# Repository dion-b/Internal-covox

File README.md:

# Internal-covox
An internal (bracket-mount) Covox Speech Thing-like card, to connect to an internal parallel header.

The Covox Speech Thing is arguably the simplest piece of sound hardware created for the PC, consisting of little more than a resistor ladder DAC and a rudimentary low-pass filter. Because of its relative rarity and extreme simplicity there are already many clone designs. The fact that the patent for the Speech Thing contains a full schematic no doubt helps as well. These clones range from extremely minimal homebrew designs to some commercial sound cards (most notably Aztech Technologies' first generation Soundblaster Pro clones) integrating the functionality.

So, why a new clone? A defining feature of the Speech Thing, and of all common clones not integrated into a sound card/chip is that they are an external design, interfacing with the parallel port of the PC. This means it can be installed without opening the PC case, and can be used on systems with no internal expansion slots. Great. But it also leads to a messy, vulnerable thing sticking out of the back of the PC. If the PC in question has internal slots and internal parallel headers, it should be possible to design something that can be mounted on an expansion slot plate that can be connected to the parallel header with a flatcable. This design is an attempt to do so.

The design is strongly inspired by Serdaco's CVX4 exernal device (available here: https://www.serdashop.com/CVX4) - which is arguably the best clone you can buy at this time - particularly in the use of 23 identical N resistors instead of 8 2N + 7 N resistors to minimise differences, and a dipswitch to modify filter and volume characteristics. Not having access to the CVX4 schematics (or indeed wanting to blatantly copy it), this design was instead based on Covox' (expired) patent. Also, not having confident skills with or equipment for SMD soldering, it is through-hole only.

An additional reason for this design is that it is my first PCB design. I wanted something simple enough for a beginner but with a real-world application. Please be forgiving of the errors here, I am most interested in critical feedback.

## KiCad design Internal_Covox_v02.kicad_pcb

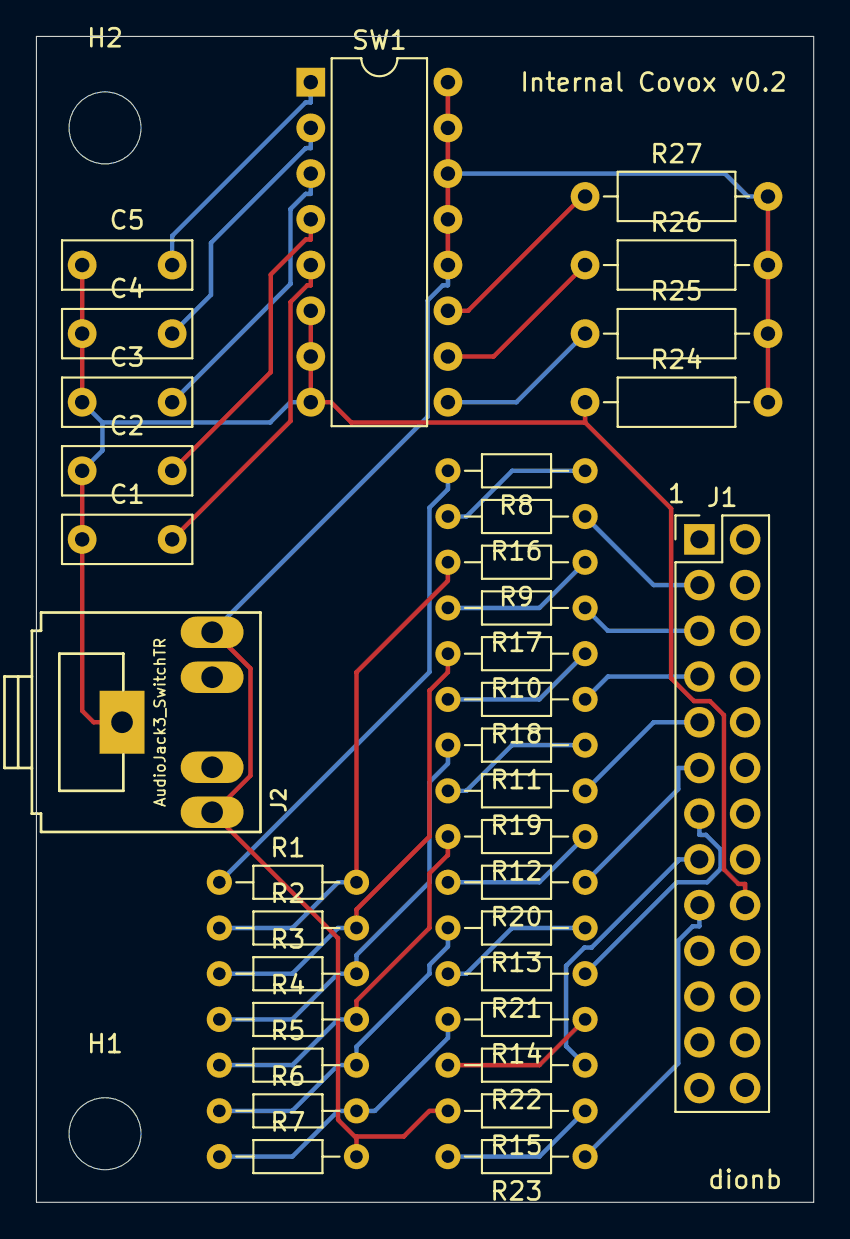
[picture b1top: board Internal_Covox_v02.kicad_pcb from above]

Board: 2 copper layers, 43.2 x 64.8 mm, 37 parts (0 on the bottom side), 33 nets.

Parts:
C1, C2, C3, C4, C5: C_Small; C_Disc_D7.0mm_W2.5mm_P5.00mm
H1, H2: MountingHole; MountingHole_4mm
J1: Conn_02x13_Odd_Even; PinHeader_2x13_P2.54mm_Vertical
J2: AudioJack3_SwitchTR; Tayda_3.5mm_stereo_TRS_jack_A-853
R1, R2, R3, R4, R5, R6, R7, R8, R9, R10, R11, R12, R13, R14, R15, R16, R17, R18, R19, R20, R21, R22, R23: 100k; R_Axial_DIN0204_L3.6mm_D1.6mm_P7.62mm_Horizontal
R24: 220k; R_Axial_DIN0207_L6.3mm_D2.5mm_P10.16mm_Horizontal
R25, R26: 57k; R_Axial_DIN0207_L6.3mm_D2.5mm_P10.16mm_Horizontal
R27: 37k; R_Axial_DIN0207_L6.3mm_D2.5mm_P10.16mm_Horizontal
SW1: SW_DIP_x08; DIP-16_W7.62mm

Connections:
GND: C1.1, C2.1, C3.1, C4.1, C5.1, J1.18, J2.S, R24.1, SW1.6, SW1.7, SW1.8
unnamed: C1.2, SW1.5
unnamed: C2.2, SW1.4
unnamed: C3.2, SW1.3
unnamed: C4.2, SW1.2
unnamed: C5.2, SW1.1
unnamed: J1.3, R16.1
unnamed: J1.5, R17.1
unnamed: J1.7, R18.1
unnamed: J1.9, R19.1
unnamed: J1.11, R20.1
unnamed: J1.13, R21.1
unnamed: J1.15, R22.1
unnamed: J1.17, R23.1
unnamed: J2.R, J2.T, R7.2, R15.2, R24.2, R25.2, R26.2, R27.2, SW1.12, SW1.13, SW1.14, SW1.15, SW1.16
unnamed: R1.1, R8.2
unnamed: R1.2, R2.1, R9.2
unnamed: R10.1, R18.2
unnamed: R2.2, R3.1, R10.2
unnamed: R11.1, R19.2
unnamed: R3.2, R4.1, R11.2
unnamed: R12.1, R20.2
unnamed: R4.2, R5.1, R12.2
unnamed: R13.1, R21.2
unnamed: R5.2, R6.1, R13.2
unnamed: R14.1, R22.2
unnamed: R6.2, R7.1, R14.2
unnamed: R15.1, R23.2
unnamed: R8.1, R16.2
unnamed: R9.1, R17.2
unnamed: R25.1, SW1.9
unnamed: R26.1, SW1.10
unnamed: R27.1, SW1.11

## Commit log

2020-06-06 EasyEDA PCB Schematic
2020-06-06 EasyEDA schematic for Internal Covox v0.1
    First prototype.
    Known bugs:
    - size for 1k resistor is incorrect (too small), will be a dog's breakfast on the PCB.
    - wrong type of capacitor selected, holes slightly too far apart.
2020-06-06 EasyEDA PCB layout for Internal Covox v0.1
2020-06-06 Gerber files for Internal Covox v0.1
